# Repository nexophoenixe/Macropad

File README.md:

# Macropad
I wanted to create a Macropad with 12 Buttons and a Scroll-Wheel. Currently Working on other projects.

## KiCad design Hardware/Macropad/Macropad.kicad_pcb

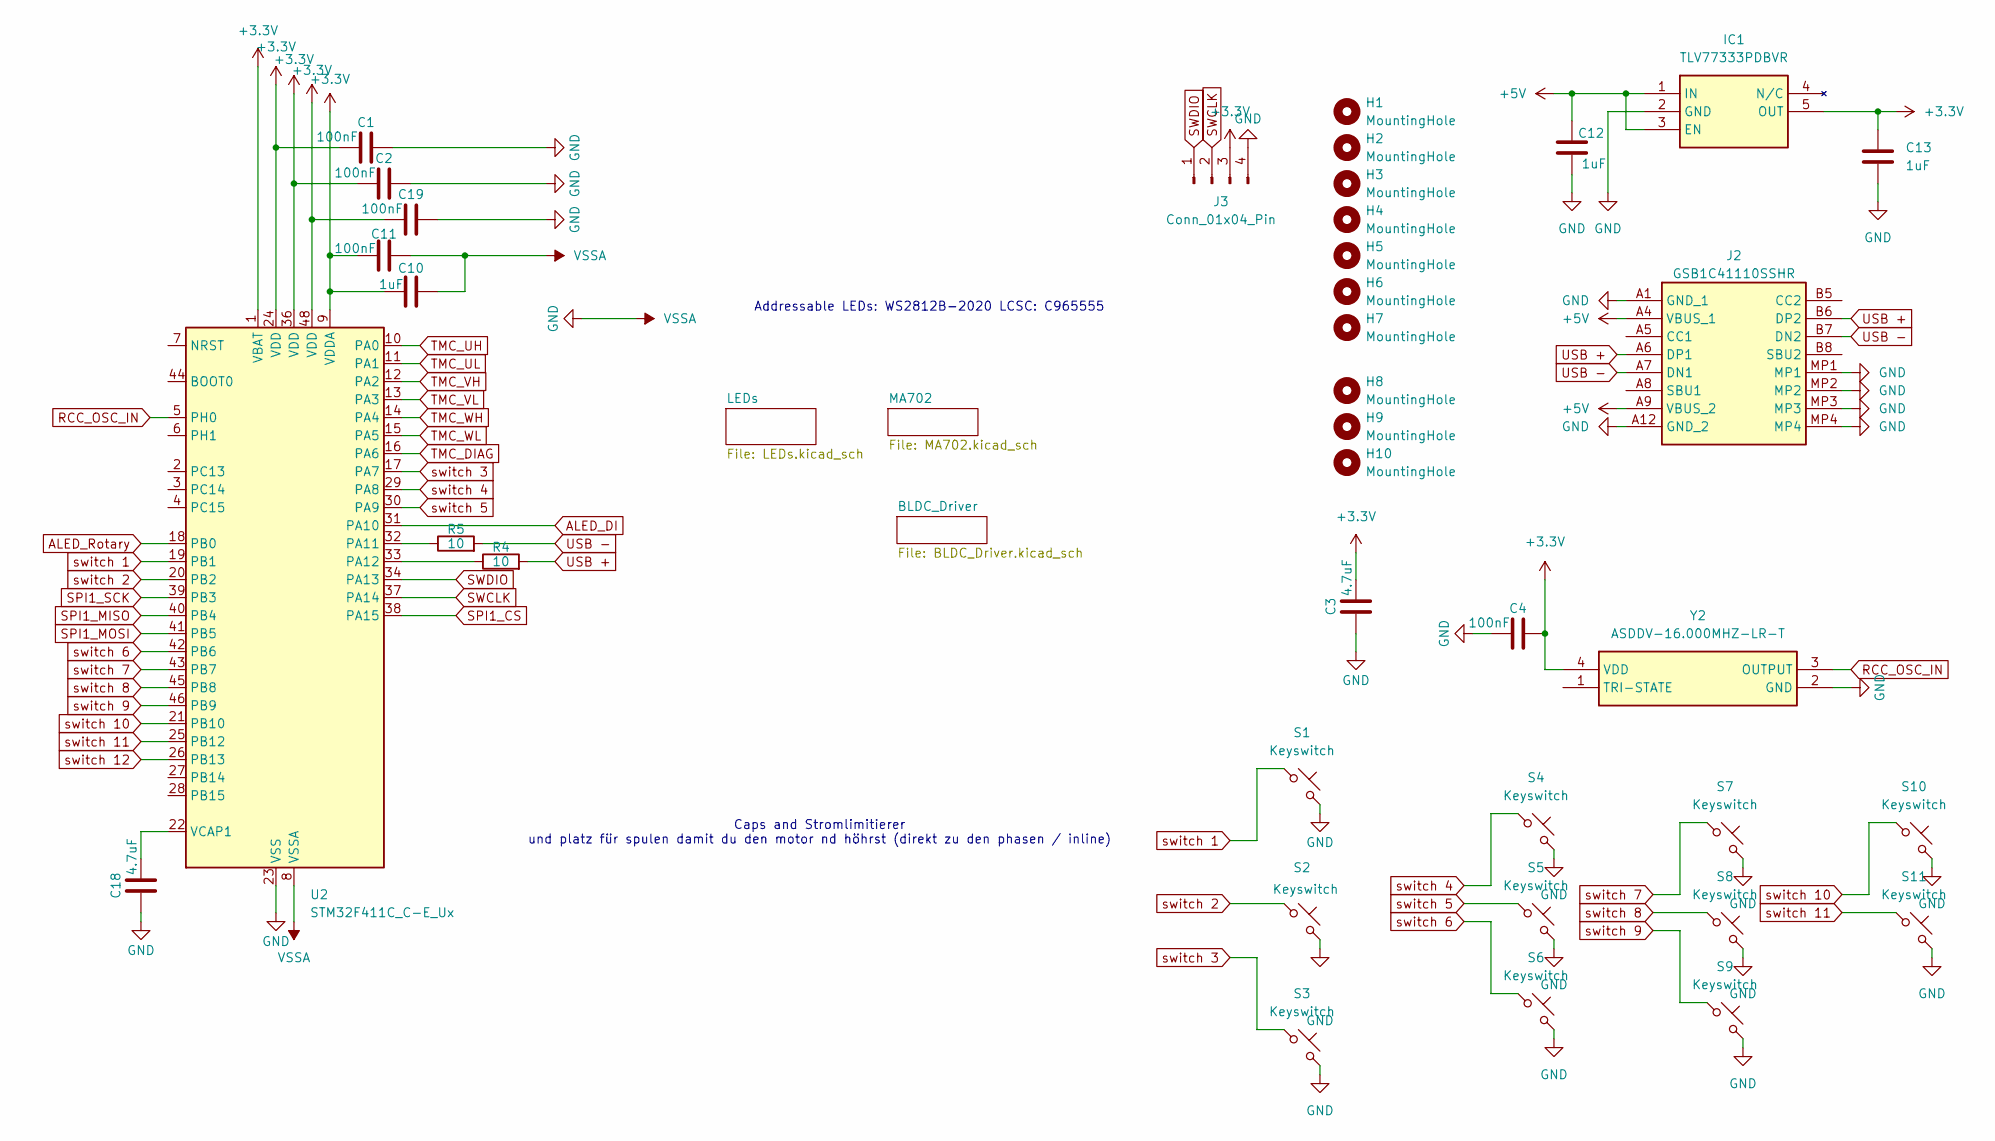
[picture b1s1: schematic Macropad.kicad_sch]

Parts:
C1, C2, C4, C11, C19: 100nF; C_0603_1608Metric
C3, C18: 4.7uF; C_0805_2012Metric
C10, C12, C13: 1uF; C_0603_1608Metric
H1, H2, H3, H4, H5, H6, H7, H8, H9, H10: MountingHole; MountingHole_2.2mm_M2
IC1: TLV77333PDBVR; SOT95P280X145-5N; Manufacturer_Part_Number TLV77333PDBVR
J2: GSB1C41110SSHR; Manufacturer_Part_Number GSB1C41110SSHR
J3: Conn_01x04_Pin; PogoPin_01x04
R4, R5: 10; R_0603_1608Metric
S1, S2, S3, S4, S5, S6, S7, S8, S9, S10, S11: Keyswitch; Kailh_socket_MX_optional
U2: STM32F411C_C-E_Ux; QFN-48-1EP_7x7mm_P0.5mm_EP5.6x5.6mm
Y2: ASDDV-16.000MHZ-LR-T; Mouser Part Number 815-ASDDV-1600MHZLRT

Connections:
+3.3V: C1.1, C2.1, C3.2, C4.2, C10.2, C11.2, C13.1, C19.1, IC1.5 (OUT), J3.3, U2.1 (VBAT), U2.9 (VDDA), U2.24 (VDD), U2.36 (VDD), U2.48 (VDD), Y2.4 (VDD); also elsewhere on the board
+5V: C12.1, IC1.1 (IN), IC1.3 (EN), J2.A4 (VBUS_1), J2.A9 (VBUS_2); also elsewhere on the board
ALED_DI: U2.31 (PA10); also elsewhere on the board
ALED_Rotary: U2.18 (PB0)
GND: C1.2, C2.2, C3.1, C4.1, C10.1, C11.1, C12.2, C13.2, C18.1, C19.2, IC1.2 (GND), J2.A1 (GND_1), J2.A12 (GND_2), J2.MP1, J2.MP2, J2.MP3, J2.MP4, J3.4, S1.2, S2.2, S3.2, S4.2, S5.2, S6.2, S7.2, S8.2, S9.2, S10.2, S11.2, U2.8 (VSSA), U2.23 (VSS), U2.35 (VSS), U2.47 (VSS), U2.49 (VSS), Y2.2 (GND); also elsewhere on the board
unnamed: R5.1, U2.32 (PA11)
unnamed: R4.1, U2.33 (PA12)
unnamed: C18.2, U2.22 (VCAP1)
RCC_OSC_IN: U2.5 (PH0), Y2.3 (OUTPUT)
SPI1_CS: U2.38 (PA15); also elsewhere on the board
SPI1_MISO: U2.40 (PB4); also elsewhere on the board
SPI1_MOSI: U2.41 (PB5); also elsewhere on the board
SPI1_SCK: U2.39 (PB3); also elsewhere on the board
SWCLK: J3.2, U2.37 (PA14)
SWDIO: J3.1, U2.34 (PA13)
TMC_DIAG: U2.16 (PA6); also elsewhere on the board
TMC_UH: U2.10 (PA0); also elsewhere on the board
TMC_UL: U2.11 (PA1); also elsewhere on the board
TMC_VH: U2.12 (PA2); also elsewhere on the board
TMC_VL: U2.13 (PA3); also elsewhere on the board
TMC_WH: U2.14 (PA4); also elsewhere on the board
TMC_WL: U2.15 (PA5); also elsewhere on the board
USB +: J2.A6 (DP1), J2.B6 (DP2), R4.2
USB -: J2.A7 (DN1), J2.B7 (DN2), R5.2
switch 1: S1.1, U2.19 (PB1)
switch 2: S2.1, U2.20 (PB2)
switch 3: S3.1, U2.17 (PA7)
switch 4: S4.1, U2.29 (PA8)
switch 5: S5.1, U2.30 (PA9)
switch 6: S6.1, U2.42 (PB6)
switch 7: S7.1, U2.43 (PB7)
switch 8: S8.1, U2.45 (PB8)
switch 9: S9.1, U2.46 (PB9)
switch 10: S10.1, U2.21 (PB10)
switch 11: S11.1, U2.25 (PB12)
switch 12: U2.26 (PB13)

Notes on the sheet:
Addressable LEDs: WS2812B-2020 LCSC: C965555
Caps and Stromlimitierer und platz für spulen damit du den motor nd höhrst (direkt zu den phasen / inline)

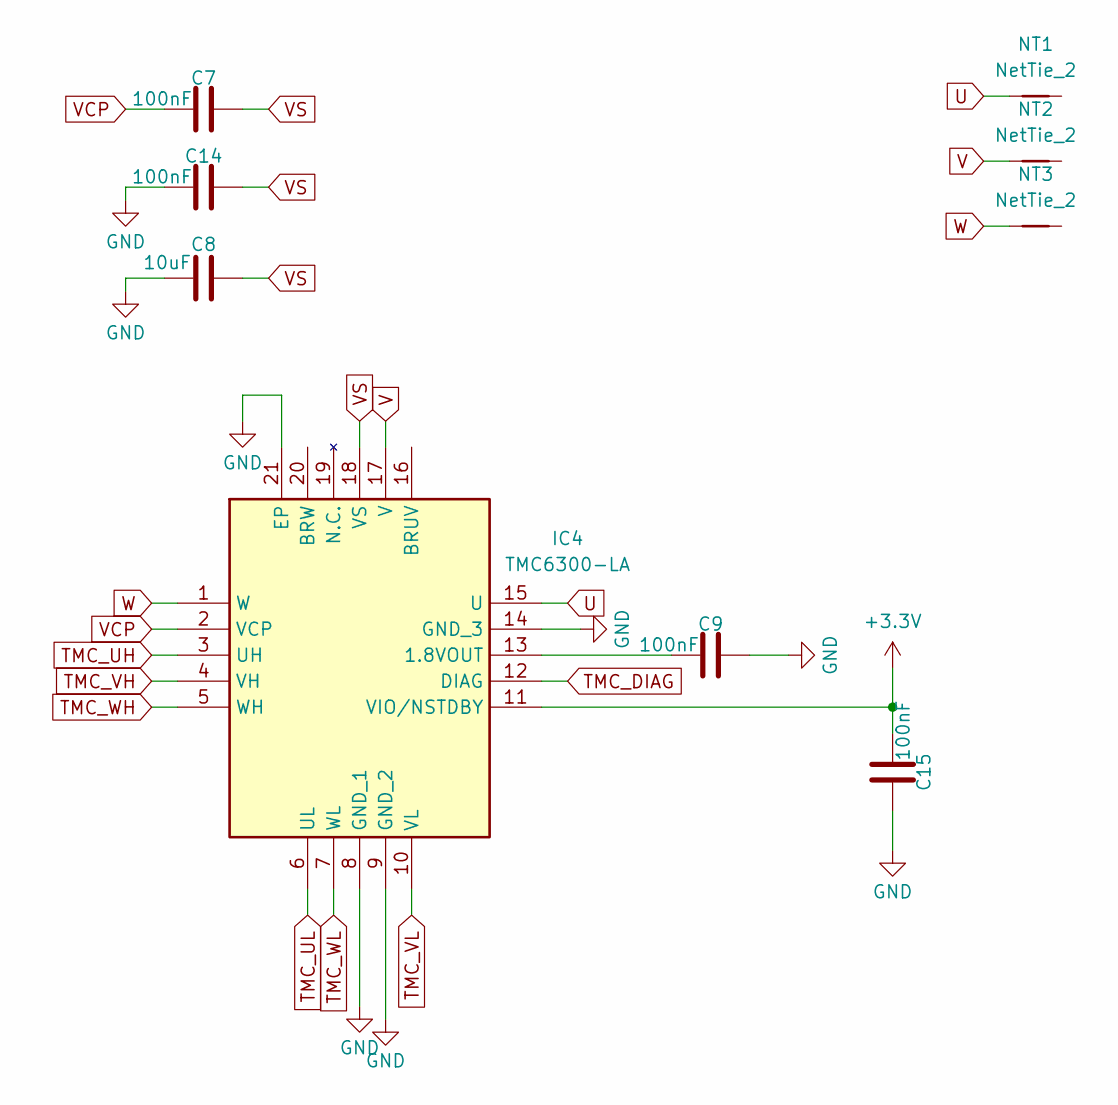
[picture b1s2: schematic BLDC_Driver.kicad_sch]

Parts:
C7, C9, C14, C15: 100nF; C_0603_1608Metric
C8: 10uF; C_0603_1608Metric
IC4: TMC6300-LA; QFN40P300X300X90-21N; Mouser Part Number 700-TMC6300-LA
NT1, NT2, NT3: NetTie_2; NetTie-2_SMD_Pad0.25mm

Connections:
+3.3V: C15.2, IC4.11 (VIO/NSTDBY); also elsewhere on the board
GND: C8.2, C9.1, C14.2, C15.1, IC4.8 (GND_1), IC4.9 (GND_2), IC4.14 (GND_3), IC4.21 (EP); also elsewhere on the board
unnamed: C9.2, IC4.13 (1.8VOUT)
TMC_DIAG: IC4.12 (DIAG); also elsewhere on the board
TMC_UH: IC4.3 (UH); also elsewhere on the board
TMC_UL: IC4.6 (UL); also elsewhere on the board
TMC_VH: IC4.4 (VH); also elsewhere on the board
TMC_VL: IC4.10 (VL); also elsewhere on the board
TMC_WH: IC4.5 (WH); also elsewhere on the board
TMC_WL: IC4.7 (WL); also elsewhere on the board
U: IC4.15 (U), NT1.1
V: IC4.17 (V), NT2.1
VCP: C7.2, IC4.2 (VCP)
VS: C7.1, C8.1, C14.1, IC4.18 (VS)
W: IC4.1 (W), NT3.1

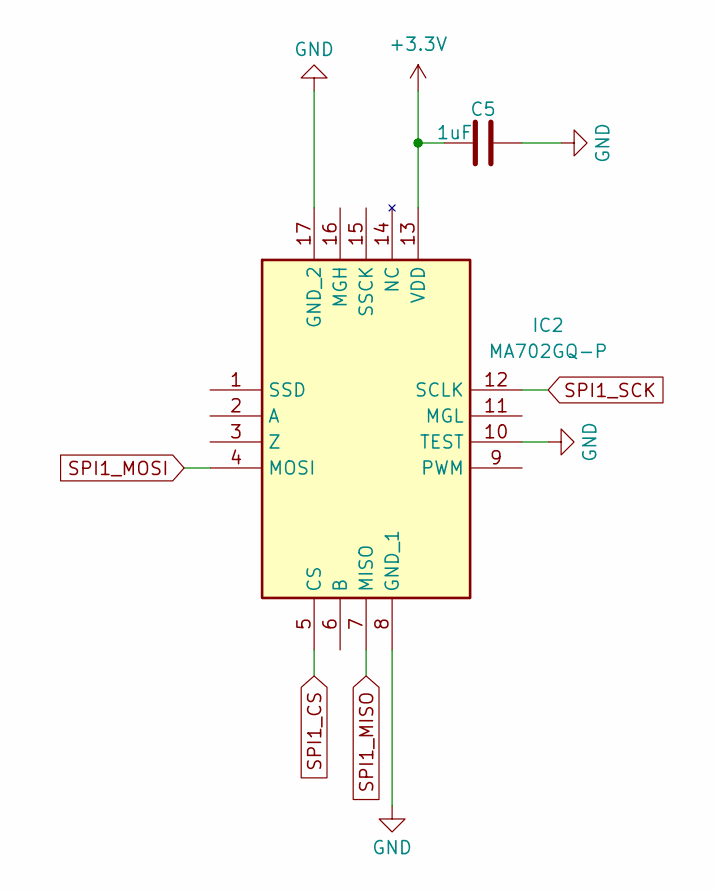
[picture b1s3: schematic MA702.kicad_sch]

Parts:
C5: 1uF; C_0603_1608Metric
IC2: MA702GQ-P; QFN50P300X300X100-17N-D; Mouser Part Number 946-MA702GQ-P

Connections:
+3.3V: C5.2, IC2.13 (VDD); also elsewhere on the board
GND: C5.1, IC2.8 (GND_1), IC2.10 (TEST), IC2.17 (GND_2); also elsewhere on the board
SPI1_CS: IC2.5 (CS); also elsewhere on the board
SPI1_MISO: IC2.7 (MISO); also elsewhere on the board
SPI1_MOSI: IC2.4 (MOSI); also elsewhere on the board
SPI1_SCK: IC2.12 (SCLK); also elsewhere on the board

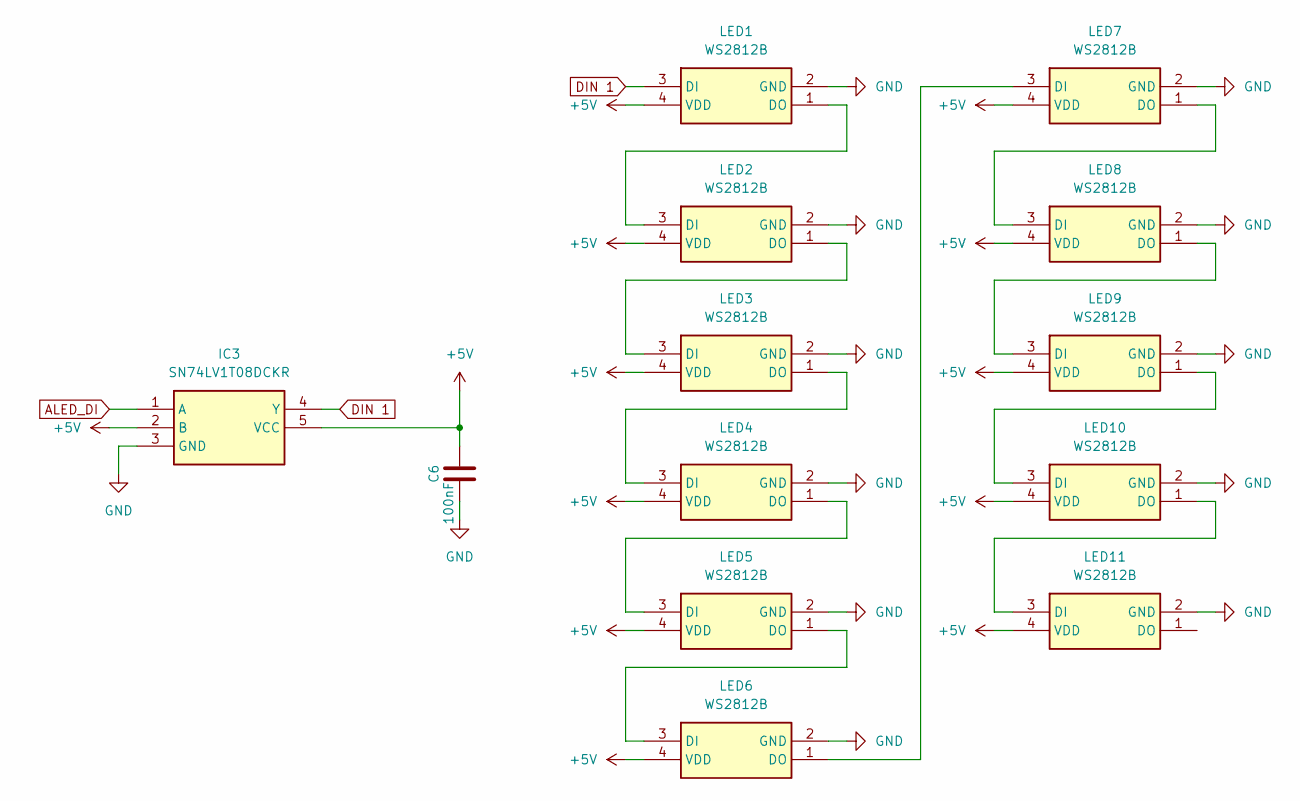
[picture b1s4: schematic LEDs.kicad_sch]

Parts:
C6: 100nF; C_0603_1608Metric
IC3: SN74LV1T08DCKR; SOT65P210X110-5N; Mouser Part Number 595-SN74LV1T08DCKR
LED1, LED2, LED3, LED4, LED5, LED6, LED7, LED8, LED9, LED10, LED11: WS2812B; XINGLIGHT XL-1515RGBC-WS2812B; Mouser Part Number 485-4684

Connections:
+5V: C6.2, IC3.2 (B), IC3.5 (VCC), LED1.4 (VDD), LED2.4 (VDD), LED3.4 (VDD), LED4.4 (VDD), LED5.4 (VDD), LED6.4 (VDD), LED7.4 (VDD), LED8.4 (VDD), LED9.4 (VDD), LED10.4 (VDD), LED11.4 (VDD); also elsewhere on the board
ALED_DI: IC3.1 (A); also elsewhere on the board
DIN 1: IC3.4 (Y), LED1.3 (DI)
GND: C6.1, IC3.3 (GND), LED1.2 (GND), LED2.2 (GND), LED3.2 (GND), LED4.2 (GND), LED5.2 (GND), LED6.2 (GND), LED7.2 (GND), LED8.2 (GND), LED9.2 (GND), LED10.2 (GND), LED11.2 (GND); also elsewhere on the board
unnamed: LED1.1 (DO), LED2.3 (DI)
unnamed: LED2.1 (DO), LED3.3 (DI)
unnamed: LED3.1 (DO), LED4.3 (DI)
unnamed: LED4.1 (DO), LED5.3 (DI)
unnamed: LED5.1 (DO), LED6.3 (DI)
unnamed: LED6.1 (DO), LED7.3 (DI)
unnamed: LED7.1 (DO), LED8.3 (DI)
unnamed: LED8.1 (DO), LED9.3 (DI)
unnamed: LED9.1 (DO), LED10.3 (DI)
unnamed: LED10.1 (DO), LED11.3 (DI)

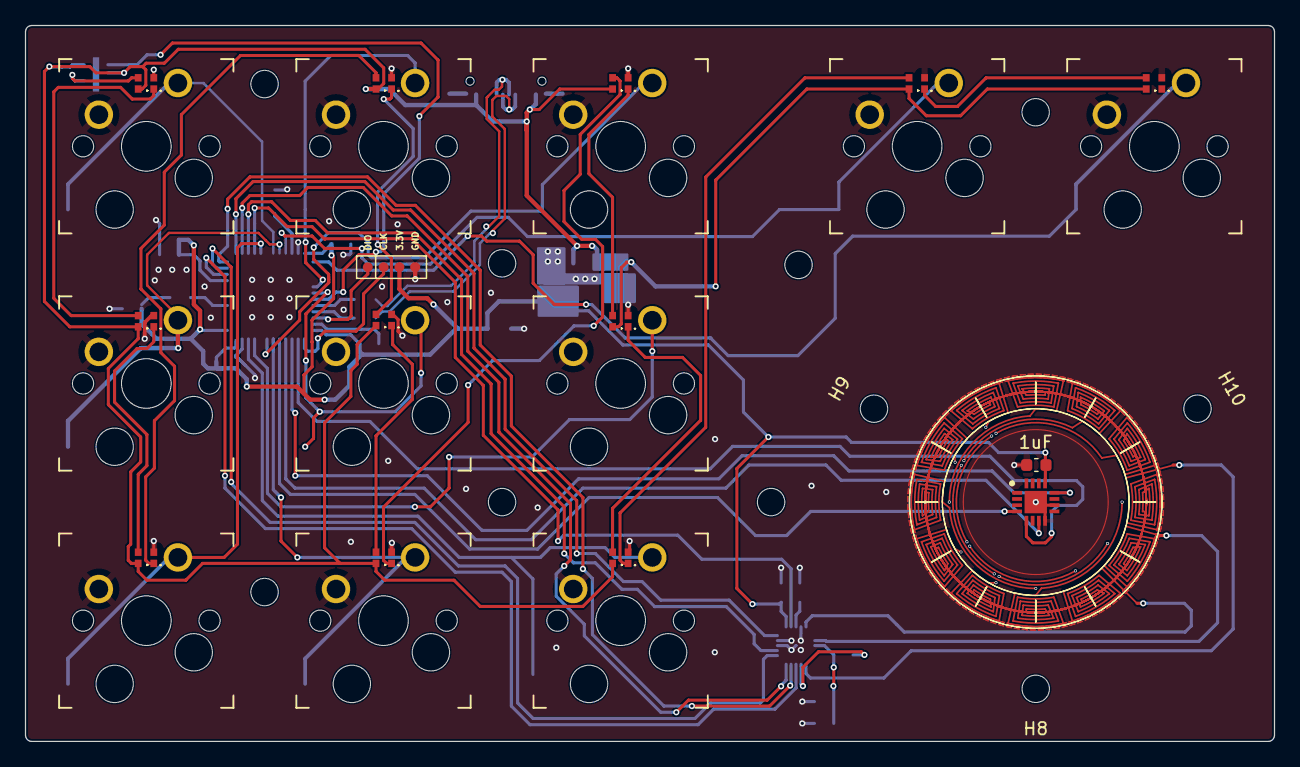
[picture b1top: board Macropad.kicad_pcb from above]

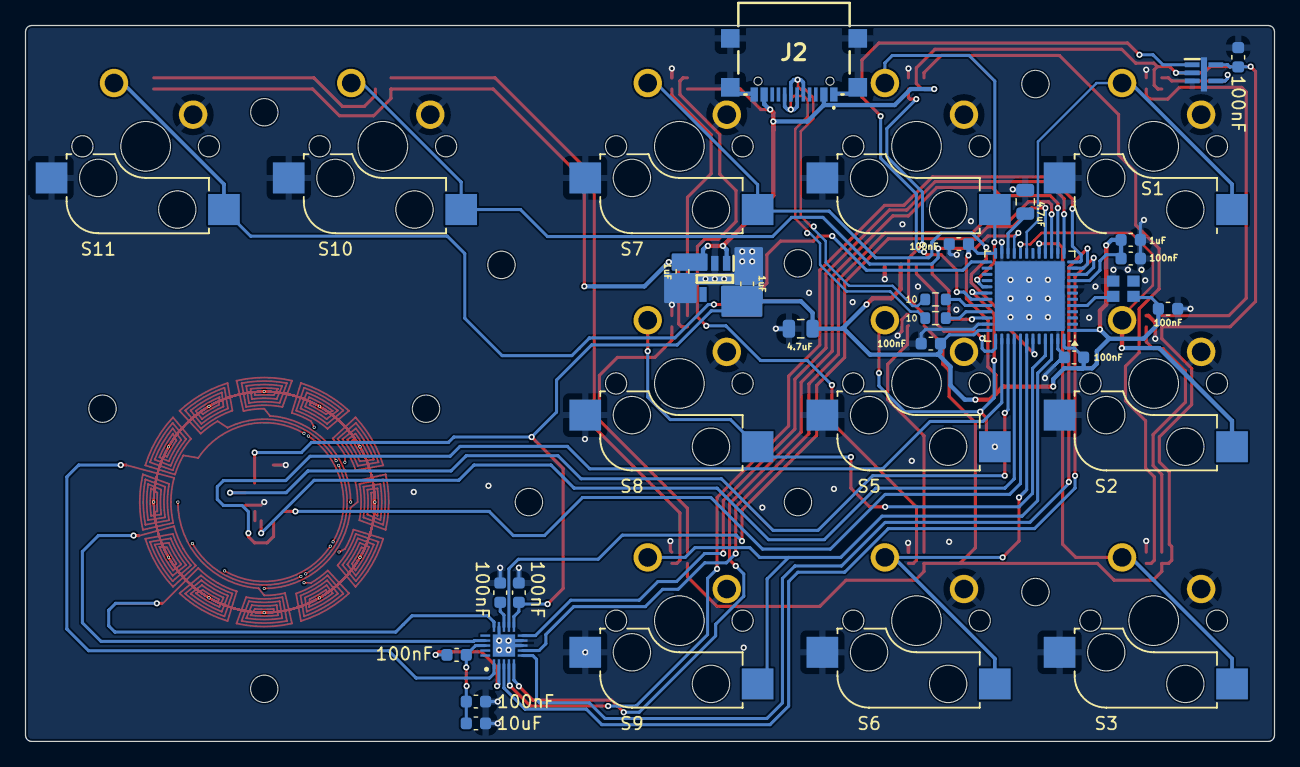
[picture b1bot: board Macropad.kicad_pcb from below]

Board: 4 copper layers, 100.3 x 57.5 mm, 62 parts (24 on the bottom side), 51 nets.

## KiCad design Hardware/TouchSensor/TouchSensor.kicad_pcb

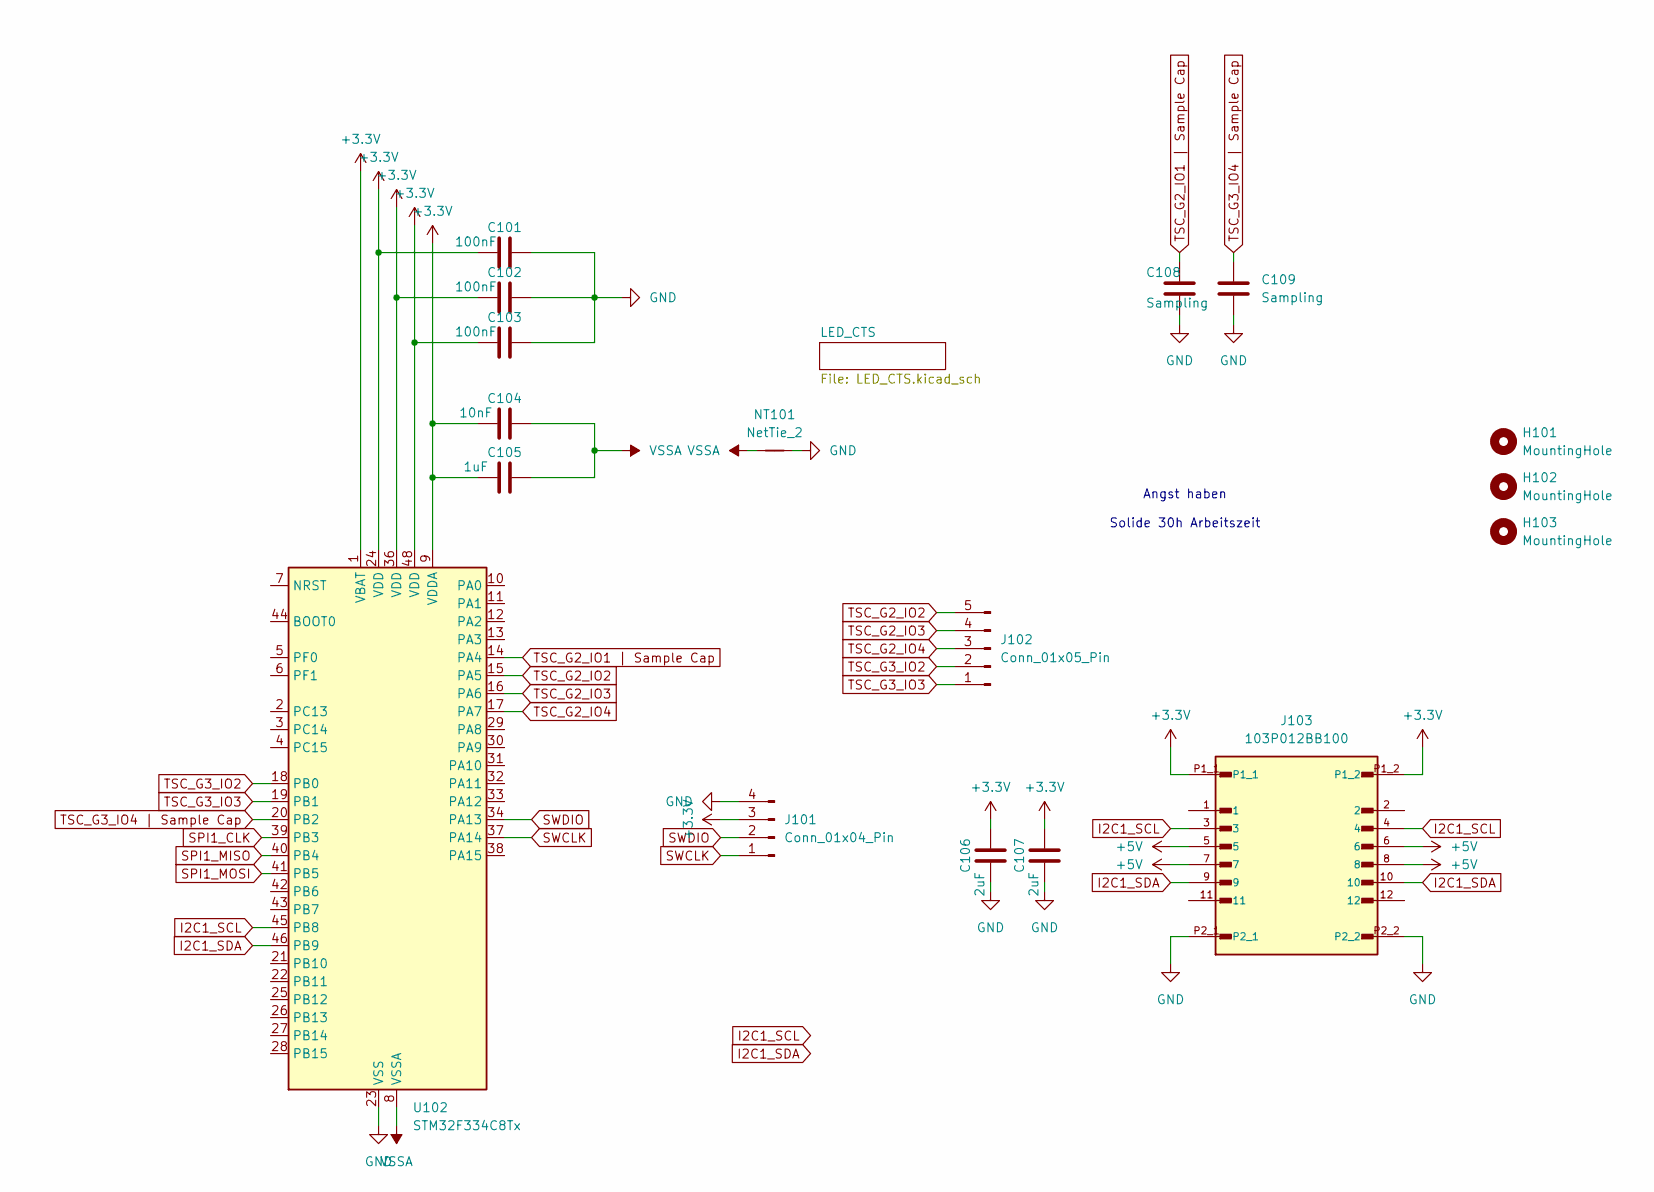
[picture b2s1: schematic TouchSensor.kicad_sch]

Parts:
C101, C102, C103: 100nF; C_0603_1608Metric
C104: 10nF; C_0402_1005Metric
C105: 1uF; C_0603_1608Metric
C106, C107: 2uF; C_0603_1608Metric
C108, C109: Sampling; C_0805_2012Metric
H101, H102, H103: MountingHole; MountingHole_2.2mm_M2
J101: Conn_01x04_Pin; PogoPin_01x04 wout holes
J102: Conn_01x05_Pin; TSL_5
J103: 103P012BB100; AMPHENOL_103P012BB100; PARTREV X4
NT101: NetTie_2; NetTie-2_SMD_Pad0.25mm
U102: STM32F334C8Tx; LQFP-48_7x7mm_P0.5mm

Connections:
+3.3V: C101.1, C102.1, C103.1, C104.1, C105.1, C106.2, C107.2, J101.3, J103.P1_1, J103.P1_2, U102.1 (VBAT), U102.9 (VDDA), U102.24 (VDD), U102.36 (VDD), U102.48 (VDD)
+5V: J103.5, J103.6, J103.7, J103.8; also elsewhere on the board
GND: C101.2, C102.2, C103.2, C106.1, C107.1, C108.2, C109.2, J101.4, J103.P2_1, J103.P2_2, NT101.2, U102.23 (VSS), U102.35 (VSS), U102.47 (VSS); also elsewhere on the board
I2C1_SCL: J103.3, J103.4, U102.45 (PB8)
I2C1_SDA: J103.9, J103.10, U102.46 (PB9)
SPI1_CLK: U102.39 (PB3)
SPI1_MISO: U102.40 (PB4)
SPI1_MOSI: U102.41 (PB5); also elsewhere on the board
SWCLK: J101.1, U102.37 (PA14)
SWDIO: J101.2, U102.34 (PA13)
TSC_G2_IO1 | Sample Cap: C108.1, U102.14 (PA4)
TSC_G2_IO2: J102.5, U102.15 (PA5)
TSC_G2_IO3: J102.4, U102.16 (PA6)
TSC_G2_IO4: J102.3, U102.17 (PA7)
TSC_G3_IO2: J102.2, U102.18 (PB0)
TSC_G3_IO3: J102.1, U102.19 (PB1)
TSC_G3_IO4 | Sample Cap: C109.1, U102.20 (PB2)
VSSA: C104.2, C105.2, NT101.1, U102.8 (VSSA)

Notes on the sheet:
Angst haben Solide 30h Arbeitszeit

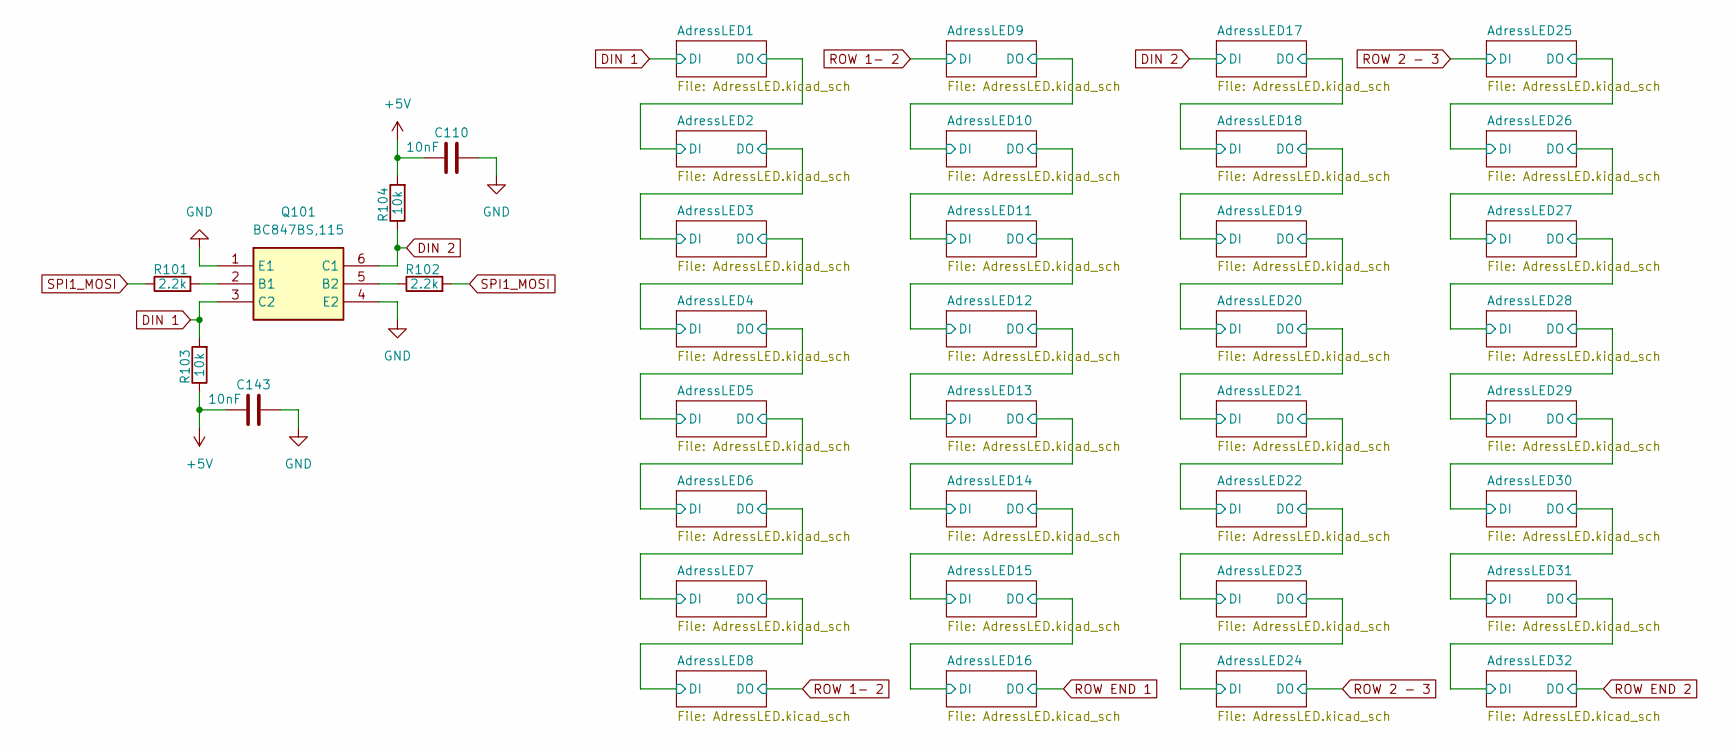
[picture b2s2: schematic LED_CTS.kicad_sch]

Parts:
C110, C143: 10nF; C_0402_1005Metric
Q101: BC847BS,115; SOT65P210X110-6N; Mouser Part Number 771-BC847BS-T/R
R101, R102: 2.2k; R_0402_1005Metric
R103, R104: 10k; R_0402_1005Metric

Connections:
+5V: C110.1, C143.1, R103.1, R104.2; also elsewhere on the board
DIN 1: Q101.3 (C2), R103.2; also elsewhere on the board
DIN 2: Q101.6 (C1), R104.1; also elsewhere on the board
GND: C110.2, C143.2, Q101.1 (E1), Q101.4 (E2); also elsewhere on the board
unnamed: Q101.2 (B1), R101.2
unnamed: Q101.5 (B2), R102.1
SPI1_MOSI: R101.1, R102.2; also elsewhere on the board

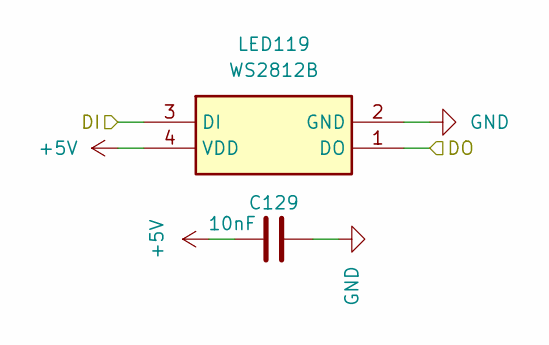
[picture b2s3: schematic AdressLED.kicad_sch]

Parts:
C129: 10nF; C_0402_1005Metric
LED119: WS2812B; XINGLIGHT XL-1515RGBC-WS2812B; Mouser Part Number 485-4684

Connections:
+5V: C129.1, LED119.4 (VDD); also elsewhere on the board
/LED_CTS/AdressLED18/DO: LED119.3 (DI); also elsewhere on the board
/LED_CTS/AdressLED19/DO: LED119.1 (DO); also elsewhere on the board
GND: C129.2, LED119.2 (GND); also elsewhere on the board

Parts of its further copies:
C111, C112, C113, C114, C115, C116, C117, C118, C119, C120, C121, C122, C123, C124, C125, C126, C127, C128, C130, C131, C132, C133, C134, C135, C136, C137, C138, C139, C140, C141, C142: 10nF; C_0402_1005Metric
LED101, LED102, LED103, LED104, LED105, LED106, LED107, LED108, LED109, LED110, LED111, LED112, LED113, LED114, LED115, LED116, LED117, LED118, LED120, LED121, LED122, LED123, LED124, LED125, LED126, LED127, LED128, LED129, LED130, LED131, LED132: WS2812B; XINGLIGHT XL-1515RGBC-WS2812B; Mouser Part Number 485-4684

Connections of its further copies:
+5V: C111.1, C112.1, C113.1, C114.1, C115.1, C116.1, C117.1, C118.1, C119.1, C120.1, C121.1, C122.1, C123.1, C124.1, C125.1, C126.1, C127.1, C128.1, C130.1, C131.1, C132.1, C133.1, C134.1, C135.1, C136.1, C137.1, C138.1, C139.1, C140.1, C141.1, C142.1, LED101.4 (VDD), LED102.4 (VDD), LED103.4 (VDD), LED104.4 (VDD), LED105.4 (VDD), LED106.4 (VDD), LED107.4 (VDD), LED108.4 (VDD), LED109.4 (VDD), LED110.4 (VDD), LED111.4 (VDD), LED112.4 (VDD), LED113.4 (VDD), LED114.4 (VDD), LED115.4 (VDD), LED116.4 (VDD), LED117.4 (VDD), LED118.4 (VDD), LED120.4 (VDD), LED121.4 (VDD), LED122.4 (VDD), LED123.4 (VDD), LED124.4 (VDD), LED125.4 (VDD), LED126.4 (VDD), LED127.4 (VDD), LED128.4 (VDD), LED129.4 (VDD), LED130.4 (VDD), LED131.4 (VDD), LED132.4 (VDD); also elsewhere on the board
/LED_CTS/AdressLED1/DO: LED101.1 (DO), LED102.3 (DI)
/LED_CTS/AdressLED2/DO: LED102.1 (DO), LED103.3 (DI)
/LED_CTS/AdressLED3/DO: LED103.1 (DO), LED104.3 (DI)
/LED_CTS/AdressLED4/DO: LED104.1 (DO), LED105.3 (DI)
/LED_CTS/AdressLED5/DO: LED105.1 (DO), LED106.3 (DI)
/LED_CTS/AdressLED6/DO: LED106.1 (DO), LED107.3 (DI)
/LED_CTS/AdressLED7/DO: LED107.1 (DO), LED108.3 (DI)
/LED_CTS/AdressLED10/DI: LED109.1 (DO), LED110.3 (DI)
/LED_CTS/AdressLED10/DO: LED110.1 (DO), LED111.3 (DI)
/LED_CTS/AdressLED11/DO: LED111.1 (DO), LED112.3 (DI)
/LED_CTS/AdressLED12/DO: LED112.1 (DO), LED113.3 (DI)
/LED_CTS/AdressLED13/DO: LED113.1 (DO), LED114.3 (DI)
/LED_CTS/AdressLED14/DO: LED114.1 (DO), LED115.3 (DI)
/LED_CTS/AdressLED15/DO: LED115.1 (DO), LED116.3 (DI)
/LED_CTS/AdressLED17/DO: LED117.1 (DO), LED118.3 (DI)
/LED_CTS/AdressLED18/DO: LED118.1 (DO); also elsewhere on the board
/LED_CTS/AdressLED19/DO: LED120.3 (DI); also elsewhere on the board
/LED_CTS/AdressLED20/DO: LED120.1 (DO), LED121.3 (DI)
/LED_CTS/AdressLED21/DO: LED121.1 (DO), LED122.3 (DI)
/LED_CTS/AdressLED22/DO: LED122.1 (DO), LED123.3 (DI)
/LED_CTS/AdressLED23/DO: LED123.1 (DO), LED124.3 (DI)
/LED_CTS/AdressLED25/DO: LED125.1 (DO), LED126.3 (DI)
/LED_CTS/AdressLED26/DO: LED126.1 (DO), LED127.3 (DI)
/LED_CTS/AdressLED27/DO: LED127.1 (DO), LED128.3 (DI)
/LED_CTS/AdressLED28/DO: LED128.1 (DO), LED129.3 (DI)
/LED_CTS/AdressLED29/DO: LED129.1 (DO), LED130.3 (DI)
/LED_CTS/AdressLED30/DO: LED130.1 (DO), LED131.3 (DI)
/LED_CTS/AdressLED31/DO: LED131.1 (DO), LED132.3 (DI)
DIN 1: LED101.3 (DI); also elsewhere on the board
DIN 2: LED117.3 (DI); also elsewhere on the board
GND: C111.2, C112.2, C113.2, C114.2, C115.2, C116.2, C117.2, C118.2, C119.2, C120.2, C121.2, C122.2, C123.2, C124.2, C125.2, C126.2, C127.2, C128.2, C130.2, C131.2, C132.2, C133.2, C134.2, C135.2, C136.2, C137.2, C138.2, C139.2, C140.2, C141.2, C142.2, LED101.2 (GND), LED102.2 (GND), LED103.2 (GND), LED104.2 (GND), LED105.2 (GND), LED106.2 (GND), LED107.2 (GND), LED108.2 (GND), LED109.2 (GND), LED110.2 (GND), LED111.2 (GND), LED112.2 (GND), LED113.2 (GND), LED114.2 (GND), LED115.2 (GND), LED116.2 (GND), LED117.2 (GND), LED118.2 (GND), LED120.2 (GND), LED121.2 (GND), LED122.2 (GND), LED123.2 (GND), LED124.2 (GND), LED125.2 (GND), LED126.2 (GND), LED127.2 (GND), LED128.2 (GND), LED129.2 (GND), LED130.2 (GND), LED131.2 (GND), LED132.2 (GND); also elsewhere on the board
ROW 1- 2: LED108.1 (DO), LED109.3 (DI)
ROW 2 - 3: LED124.1 (DO), LED125.3 (DI)
ROW END 1: LED116.1 (DO)
ROW END 2: LED132.1 (DO)

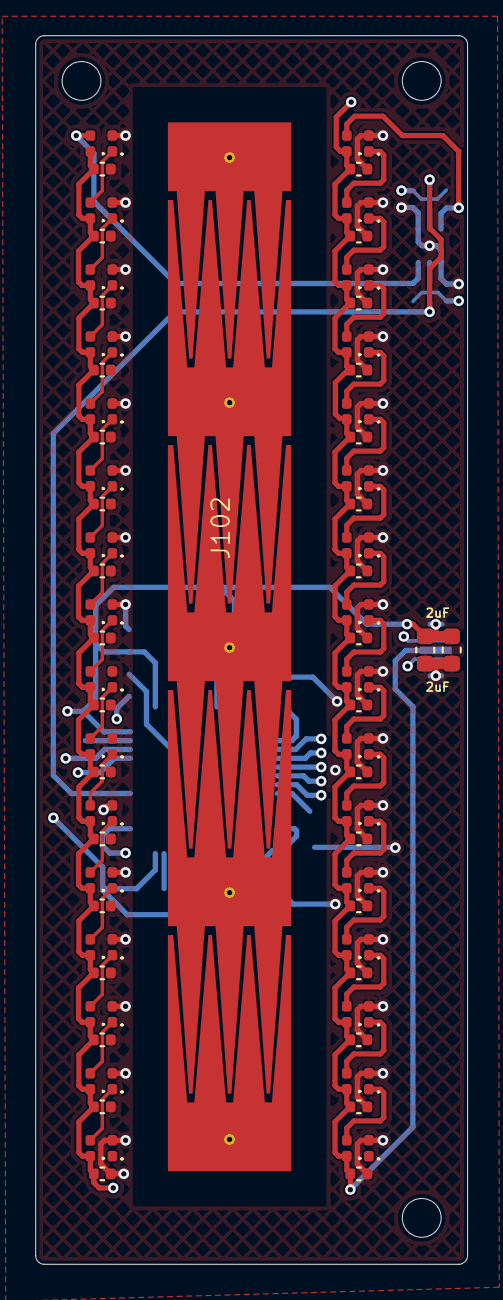
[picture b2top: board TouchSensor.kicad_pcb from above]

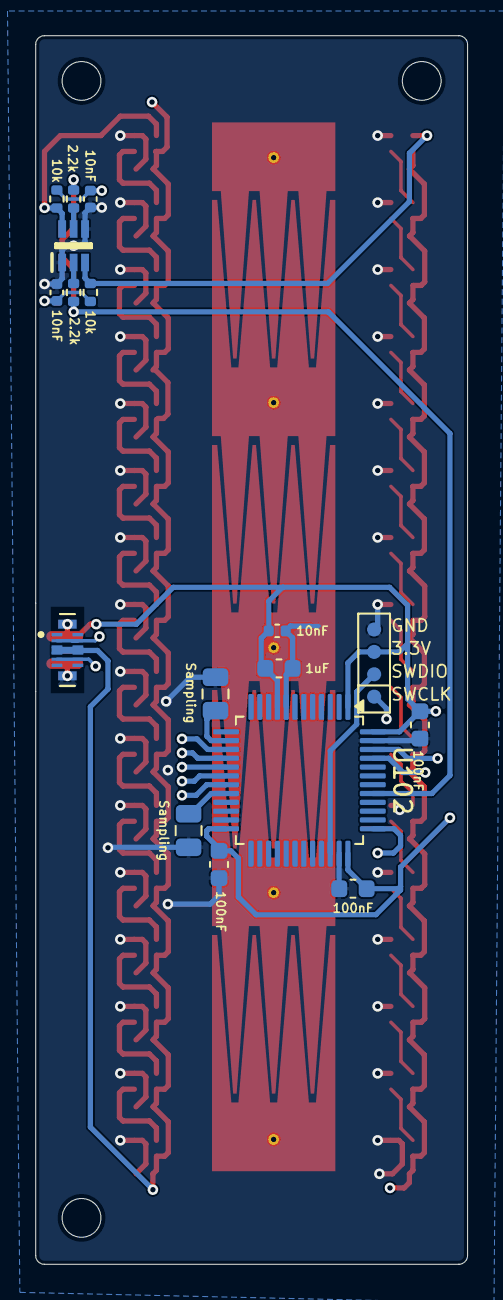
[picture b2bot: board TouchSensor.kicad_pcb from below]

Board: 4 copper layers, 24.5 x 69.7 mm, 88 parts (18 on the bottom side), 50 nets.

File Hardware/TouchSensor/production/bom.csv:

Designator,Footprint,Quantity,Value,LCSC Part #
"C101, C102, C103",0603,3,100nF,
"C104, C110, C111, C112, C113, C114, C115, C116, C117, C118, C119, C120, C121, C122, C123, C124, C125, C126, C127, C128, C129, C130, C131, C132, C133, C134, C135, C136, C137, C138, C139, C140, C141, C142, C143",0402,35,10nF,
C105,0603,1,1uF,
"C106, C107",0603,2,2uF,
"C108, C109",0805,2,Sampling,
J101,PogoPin_01x04 wout holes,1,Conn_01x04_Pin,
J102,TSL_5,1,Conn_01x05_Pin,
J103,AMPHENOL_103P012BB100,1,103P012BB100,
"LED101, LED102, LED103, LED104, LED105, LED106, LED107, LED108, LED109, LED110, LED111, LED112, LED113, LED114, LED115, LED116, LED117, LED118, LED119, LED120, LED121, LED122, LED123, LED124, LED125, LED126, LED127, LED128, LED129, LED130, LED131, LED132",XINGLIGHT XL-1515RGBC-WS2812B,32,WS2812B,
Q101,SOT65P210X110-6N,1,"BC847BS,115",
"R101, R102",0402,2,2.2k,
"R103, R104",0402,2,10k,
U102,LQFP-48_7x7mm_P0.5mm,1,STM32F334C8Tx,

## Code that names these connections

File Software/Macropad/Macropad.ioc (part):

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Mcu.Name=STM32F411C(C-E)Ux
Mcu.Package=UFQFPN48
Mcu.UserName=STM32F411CCUx
PA0-WKUP.Signal=GPIO_Output
PA1.Signal=GPIO_Output
PA10.Signal=S_TIM1_CH3
PA11.Mode=Device_Only
PA11.Signal=USB_OTG_FS_DM
PA12.Mode=Device_Only
PA12.Signal=USB_OTG_FS_DP
PA13.Mode=Serial_Wire
PA13.Signal=SYS_JTMS-SWDIO
PA14.Mode=Serial_Wire
PA14.Signal=SYS_JTCK-SWCLK
PA15.GPIOParameters=GPIO_Label
PA15.GPIO_Label=SP1_CS
PA15.Signal=GPIO_Output
PA2.Signal=GPIO_Output
PA3.Signal=GPIO_Output
PA4.Signal=GPIO_Output
PA5.Signal=GPIO_Output
PA6.Signal=GPIO_Input
PA7.Signal=GPIO_Input
PA8.Signal=GPIO_Input
PA9.Signal=GPIO_Input
PB0.Signal=S_TIM3_CH3
PB1.Signal=GPIO_Input
PB10.Signal=GPIO_Input
PB12.Signal=GPIO_Input
PB13.Signal=GPIO_Input
PB2.Signal=GPIO_Input
PB3.Mode=Full_Duplex_Master
PB3.Signal=SPI1_SCK
PB4.Mode=Full_Duplex_Master
PB4.Signal=SPI1_MISO
PB5.Mode=Full_Duplex_Master
PB5.Signal=SPI1_MOSI
PB6.Signal=GPIO_Input
PB7.Signal=GPIO_Input
PB8.Signal=GPIO_Input
PB9.Signal=GPIO_Input
PH0\ -\ OSC_IN.Mode=HSE-External-Clock-Source
PH0\ -\ OSC_IN.Signal=RCC_OSC_IN
PH1\ -\ OSC_OUT.Mode=HSE-External-Clock-Source
PH1\ -\ OSC_OUT.Signal=RCC_OSC_OUT
RCC.HSE_VALUE=16000000
RCC.SYSCLKFreq_VALUE=96000000
RCC.SYSCLKSource=RCC_SYSCLKSOURCE_PLLCLK
board=custom

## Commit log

2025-11-17 edit Hardware
2025-11-18 first Software
2025-11-18 Software
2025-12-16 wokring keypresses
2025-12-16 added TouchSensor
2026-02-24 Added Wheel
2026-02-24 Updated KiCad 8 to 9
